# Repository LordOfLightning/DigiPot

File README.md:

# DigiPot
Electronicaly controllable wide range digital potentiometer

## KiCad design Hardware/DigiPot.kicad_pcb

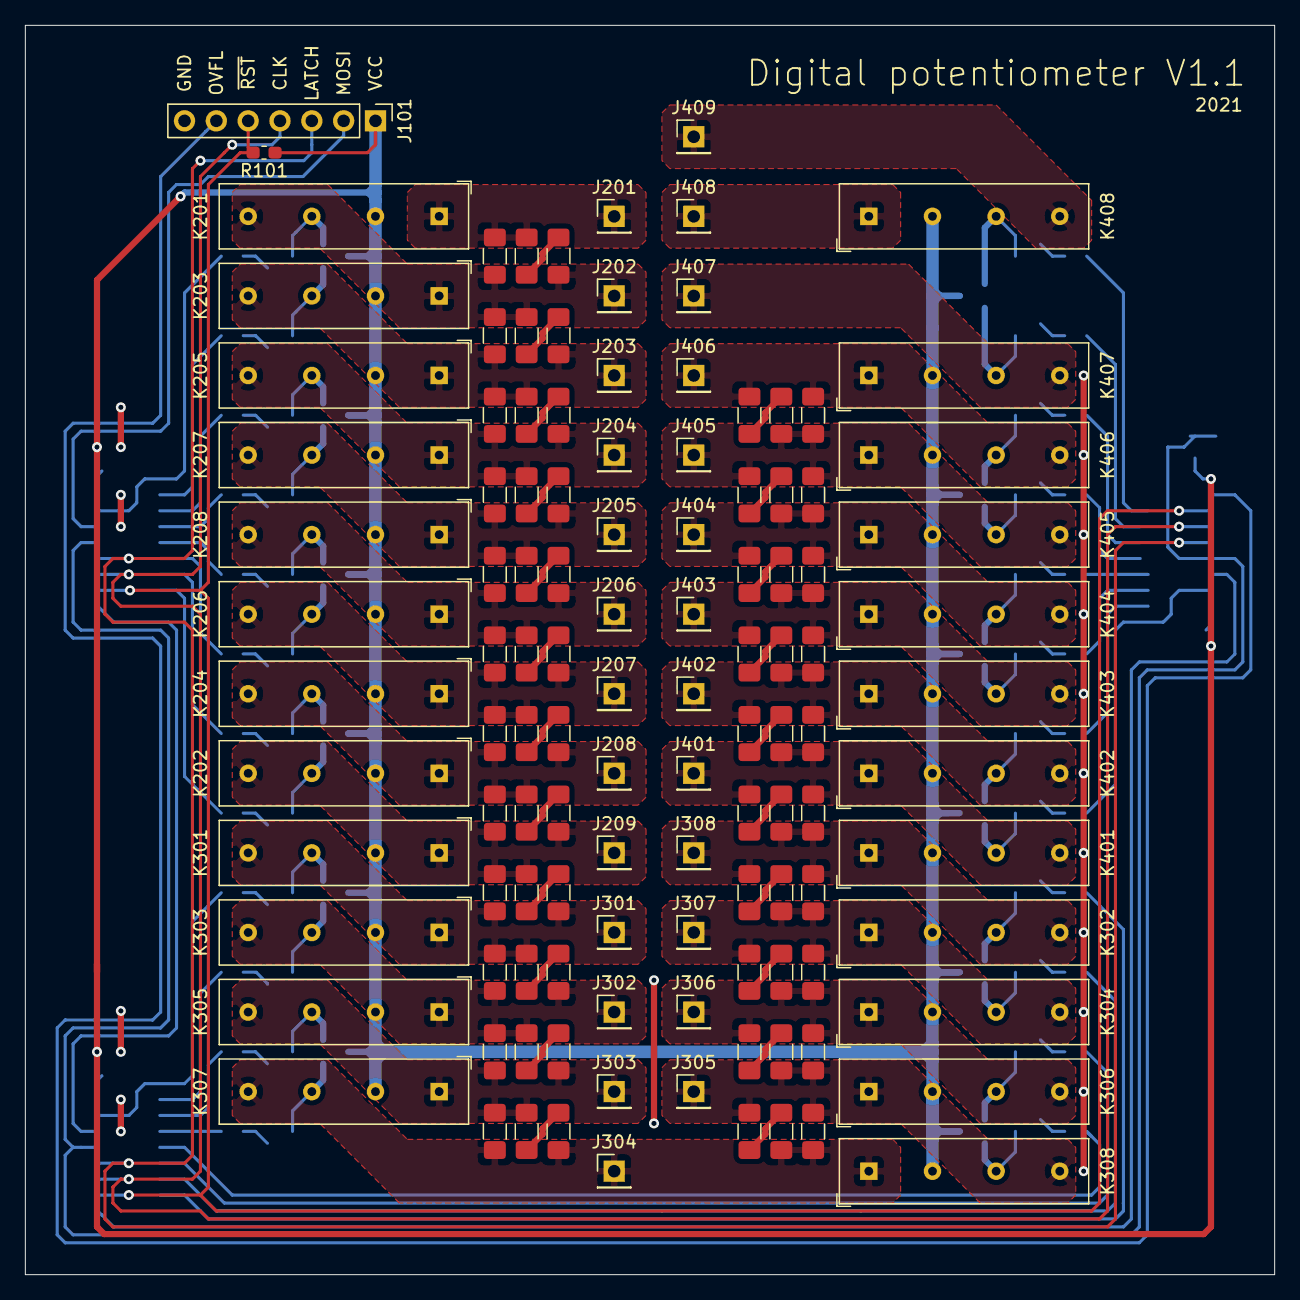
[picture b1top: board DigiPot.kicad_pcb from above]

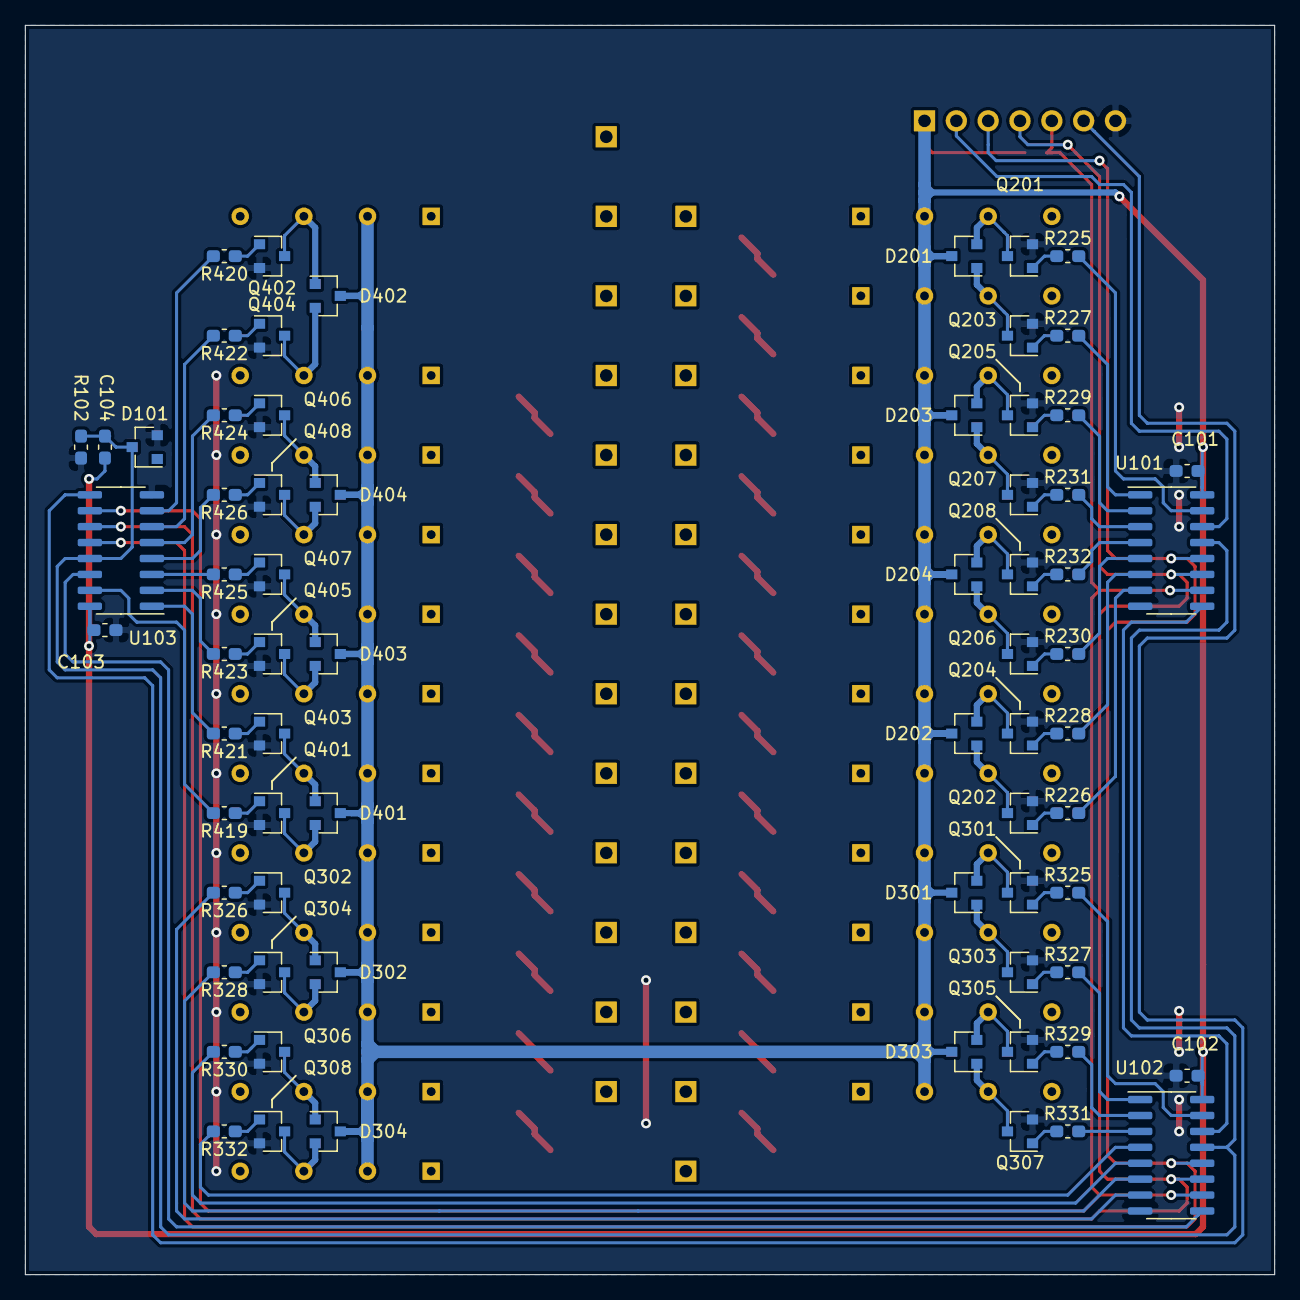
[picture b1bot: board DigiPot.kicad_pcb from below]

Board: 2 copper layers, 99.7 x 99.7 mm, 187 parts (69 on the bottom side), 130 nets.

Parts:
C101, C102, C103, C104: C; C_0603_1608Metric_Pad1.05x0.95mm_HandSolder
D101: D_Schottky_AAK; SOT-23
D201, D202, D203, D204, D301, D302, D303, D304, D401, D402, D403, D404: BAT54C; SOT-23
J101: Conn_01x07; PinHeader_1x07_P2.54mm_Vertical
J201, J202, J203, J204, J205, J206, J207, J208, J209, J301, J302, J303, J304, J305, J306, J307, J308, J401, J402, J403, J404, J405, J406, J407, J408, J409: Conn_01x01; PinHeader_1x01_P2.54mm_Vertical
K201, K202, K203, K204, K205, K206, K207, K208, K301, K302, K303, K304, K305, K306, K307, K308, K401, K402, K403, K404, K405, K406, K407, K408: SILxx-1Axx-71x; Relay_SPST_StandexMeder_SIL_Form1A
Q201, Q202, Q203, Q204, Q205, Q206, Q207, Q208, Q301, Q302, Q303, Q304, Q305, Q306, Q307, Q308, Q401, Q402, Q403, Q404, Q405, Q406, Q407, Q408: BC847; SOT-23
R101, R102, R225, R226, R227, R228, R229, R230, R231, R232, R325, R326, R327, R328, R329, R330, R331, R332, R419, R420, R421, R422, R423, R424, R425, R426: R; R_0603_1608Metric_Pad1.05x0.95mm_HandSolder
R201, R202, R203, R204, R205, R206, R207, R208, R209, R210, R211, R212, R213, R214, R215, R216, R217, R218, R219, R220, R221, R222, R223, R224, R301, R302, R303, R304, R305, R306, R307, R308, R309, R310, R311, R312, R313, R314, R315, R316, R317, R318, R319, R320, R321, R322, R323, R324, R401, R402, R403, R404, R405, R406, R407, R408, R409, R410, R411, R412, R413, R414, R415, R416, R417, R418: R; R_1206_3216Metric_Pad1.42x1.75mm_HandSolder
U101, U102, U103: 74HC595; SOIC-16_3.9x9.9mm_P1.27mm

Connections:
+5V: C101.1, C102.1, C103.1, C104.1, D201.3, D202.3, D203.3, D204.3, D301.3, D302.3, D303.3, D304.3, D401.3, D402.3, D403.3, D404.3, J101.1, K201.3, K202.3, K203.3, K204.3, K205.3, K206.3, K207.3, K208.3, K301.3, K302.3, K303.3, K304.3, K305.3, K306.3, K307.3, K308.3, K401.3, K402.3, K403.3, K404.3, K405.3, K406.3, K407.3, K408.3, R101.1, U101.16, U102.16, U103.16
/~OE: C104.2, D101.3, R102.1, U101.13, U102.13, U103.13
CLK: J101.4, U101.11, U102.11, U103.11
GND: C101.2, C102.2, C103.2, D101.2, J101.7, Q201.2, Q202.2, Q203.2, Q204.2, Q205.2, Q206.2, Q207.2, Q208.2, Q301.2, Q302.2, Q303.2, Q304.2, Q305.2, Q306.2, Q307.2, Q308.2, Q401.2, Q402.2, Q403.2, Q404.2, Q405.2, Q406.2, Q407.2, Q408.2, R102.2, U101.8, U102.8, U103.8
LATCH: J101.3, U101.12, U102.12, U103.12
LSB_OUT: J308.1, K302.7, K401.1, R316.1, R324.2, R401.1, R413.2
MOSI: J101.2, U101.14
MSB_OUT: J209.1, K202.7, K301.1, R216.1, R224.2, R301.1, R317.2
unnamed: D201.1, K203.5, Q203.3
unnamed: D201.2, K201.5, Q201.3
unnamed: D202.1, K202.5, Q202.3
unnamed: D202.2, K204.5, Q204.3
unnamed: D203.1, K207.5, Q207.3
unnamed: D203.2, K205.5, Q205.3
unnamed: D204.1, K206.5, Q206.3
unnamed: D204.2, K208.5, Q208.3
unnamed: D301.1, K303.5, Q303.3
unnamed: D301.2, K301.5, Q301.3
unnamed: D302.1, K302.5, Q302.3
unnamed: D302.2, K304.5, Q304.3
unnamed: D303.1, K307.5, Q307.3
unnamed: D303.2, K305.5, Q305.3
unnamed: D304.1, K306.5, Q306.3
unnamed: D304.2, K308.5, Q308.3
unnamed: D401.1, K402.5, Q403.3
unnamed: D401.2, K401.5, Q401.3
unnamed: D402.1, K408.5, Q402.3
unnamed: D402.2, K407.5, Q404.3
unnamed: D403.1, K404.5, Q407.3
unnamed: D403.2, K403.5, Q405.3
unnamed: D404.1, K406.5, Q406.3
unnamed: D404.2, K405.5, Q408.3
unnamed: J201.1, K201.1, R201.1, R217.2
unnamed: J202.1, K201.7, K203.1, R202.1, R203.1, R217.1, R218.2
unnamed: J203.1, K203.7, K205.1, R204.1, R205.1, R218.1, R219.2
unnamed: J204.1, K205.7, K207.1, R206.1, R207.1, R219.1, R220.2
unnamed: J205.1, K207.7, K208.1, R208.1, R209.1, R220.1, R221.1
unnamed: J206.1, K206.1, K208.7, R210.1, R211.1, R221.2, R222.1
unnamed: J207.1, K204.1, K206.7, R212.1, R213.1, R222.2, R223.1
unnamed: J208.1, K202.1, K204.7, R214.1, R215.1, R223.2, R224.1
unnamed: J301.1, K301.7, K303.1, R302.1, R303.1, R317.1, R318.2
unnamed: J302.1, K303.7, K305.1, R304.1, R305.1, R318.1, R319.2
unnamed: J303.1, K305.7, K307.1, R306.1, R307.1, R319.1, R320.2
unnamed: J304.1, K307.7, K308.1, R308.1, R309.1, R320.1, R321.1
unnamed: J305.1, K306.1, K308.7, R310.1, R311.1, R321.2, R322.1
unnamed: J306.1, K304.1, K306.7, R312.1, R313.1, R322.2, R323.1
unnamed: J307.1, K302.1, K304.7, R314.1, R315.1, R323.2, R324.1
unnamed: J401.1, K401.7, K402.1, R402.1, R403.1, R413.1, R414.2
unnamed: J402.1, K402.7, K403.1, R404.1, R405.1, R414.1, R415.2
unnamed: J403.1, K403.7, K404.1, R406.1, R407.1, R415.1, R416.2
unnamed: J404.1, K404.7, K405.1, R408.1, R409.1, R416.1, R417.1
unnamed: J405.1, K405.7, K406.1, R410.1, R411.1, R417.2, R418.1
unnamed: J406.1, K406.7, K407.1, R412.1, R418.2
unnamed: J407.1, K407.7
unnamed: J408.1, K408.1
unnamed: J409.1, K408.7
unnamed: Q201.1, R225.1
unnamed: Q202.1, R226.1
unnamed: Q203.1, R227.1
unnamed: Q204.1, R228.1
unnamed: Q205.1, R229.1
unnamed: Q206.1, R230.1
unnamed: Q207.1, R231.1
unnamed: Q208.1, R232.1
unnamed: Q301.1, R325.1
unnamed: Q302.1, R326.1
unnamed: Q303.1, R327.1
unnamed: Q304.1, R328.1
unnamed: Q305.1, R329.1
unnamed: Q306.1, R330.1
unnamed: Q307.1, R331.1
unnamed: Q308.1, R332.1
unnamed: Q401.1, R419.1
unnamed: Q402.1, R420.1
unnamed: Q403.1, R421.1
unnamed: Q404.1, R422.1
unnamed: Q405.1, R423.1
unnamed: Q406.1, R424.1
unnamed: Q407.1, R425.1
unnamed: Q408.1, R426.1
unnamed: R201.2, R202.2
unnamed: R203.2, R204.2
unnamed: R205.2, R206.2
unnamed: R207.2, R208.2
unnamed: R209.2, R210.2
unnamed: R211.2, R212.2
unnamed: R213.2, R214.2
unnamed: R215.2, R216.2
unnamed: R301.2, R302.2
unnamed: R303.2, R304.2
unnamed: R305.2, R306.2
unnamed: R307.2, R308.2
unnamed: R309.2, R310.2
unnamed: R311.2, R312.2
unnamed: R313.2, R314.2
unnamed: R315.2, R316.2
unnamed: R401.2, R402.2
unnamed: R403.2, R404.2
unnamed: R405.2, R406.2
unnamed: R407.2, R408.2
unnamed: R409.2, R410.2
unnamed: R411.2, R412.2
unnamed: U101.9, U102.14
unnamed: U102.9, U103.14
OVFL: J101.6, U103.9
QA1: R225.2, U101.15
QA2: R325.2, U102.15
QA3: R419.2, U103.15
QB1: R227.2, U101.1
QB2: R327.2, U102.1
QB3: R421.2, U103.1
QC1: R229.2, U101.2
QC2: R329.2, U102.2
QC3: R423.2, U103.2
QD1: R231.2, U101.3
QD2: R331.2, U102.3
QD3: R425.2, U103.3
QE1: R232.2, U101.4
QE2: R332.2, U102.4
QE3: R426.2, U103.4
QF1: R230.2, U101.5
QF2: R330.2, U102.5
QF3: R424.2, U103.5
QG1: R228.2, U101.6
QG2: R328.2, U102.6
QG3: R422.2, U103.6
QH1: R226.2, U101.7
QH2: R326.2, U102.7
QH3: R420.2, U103.7
~RST: J101.5, R101.2, U101.10, U102.10, U103.10

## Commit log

2021-11-12 Initial upload
